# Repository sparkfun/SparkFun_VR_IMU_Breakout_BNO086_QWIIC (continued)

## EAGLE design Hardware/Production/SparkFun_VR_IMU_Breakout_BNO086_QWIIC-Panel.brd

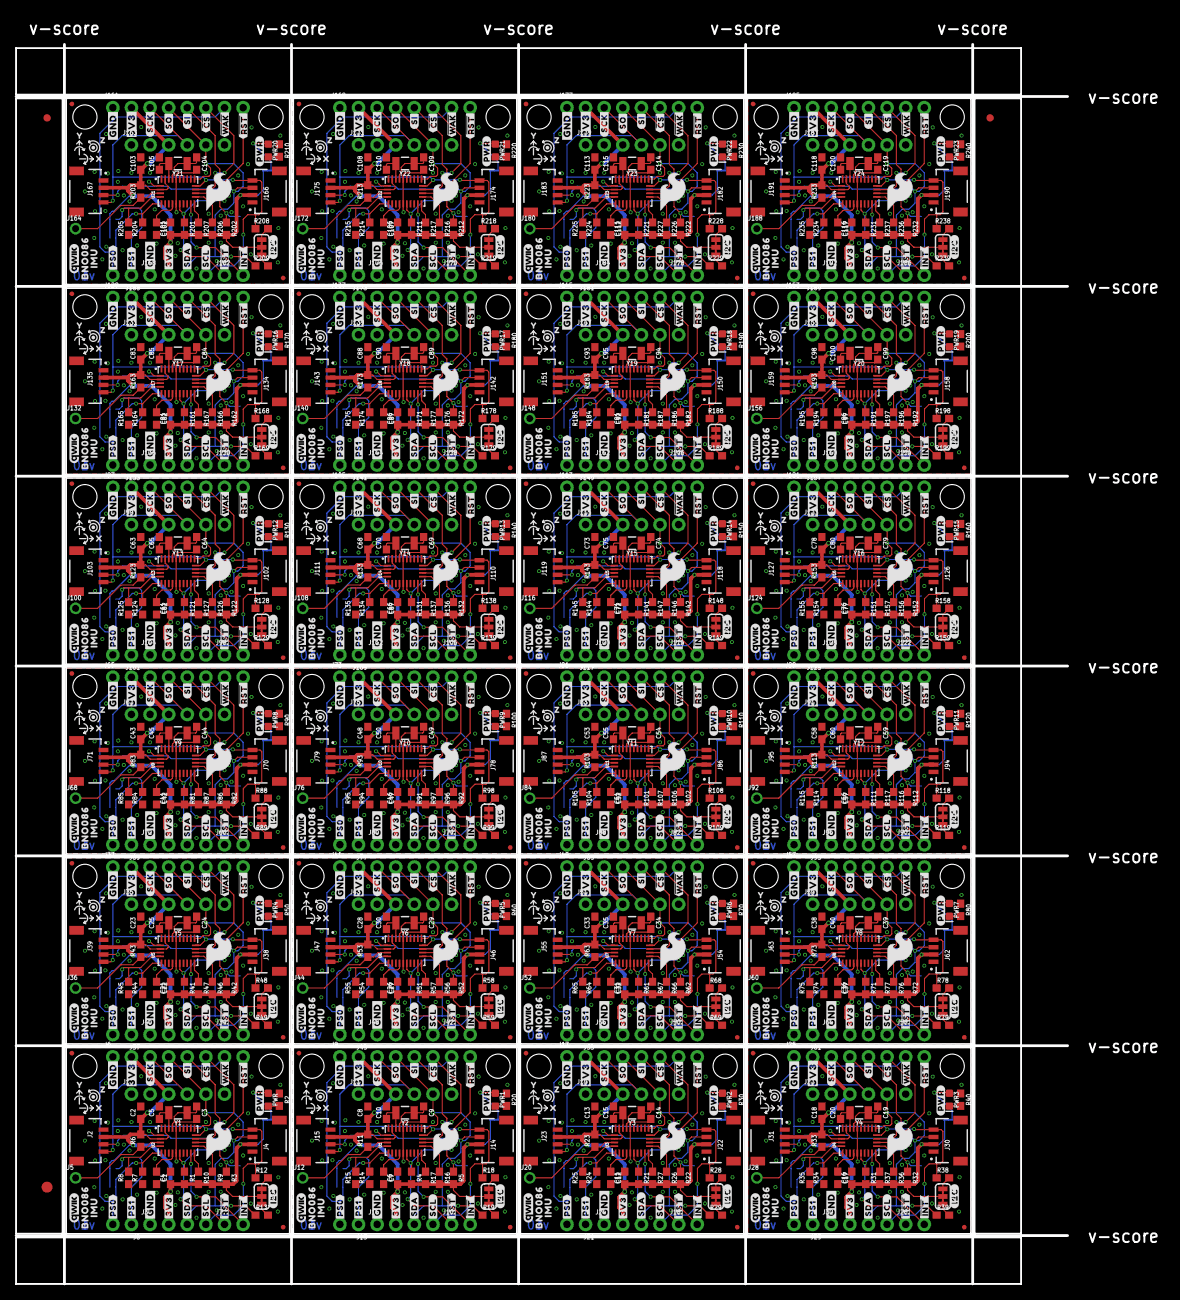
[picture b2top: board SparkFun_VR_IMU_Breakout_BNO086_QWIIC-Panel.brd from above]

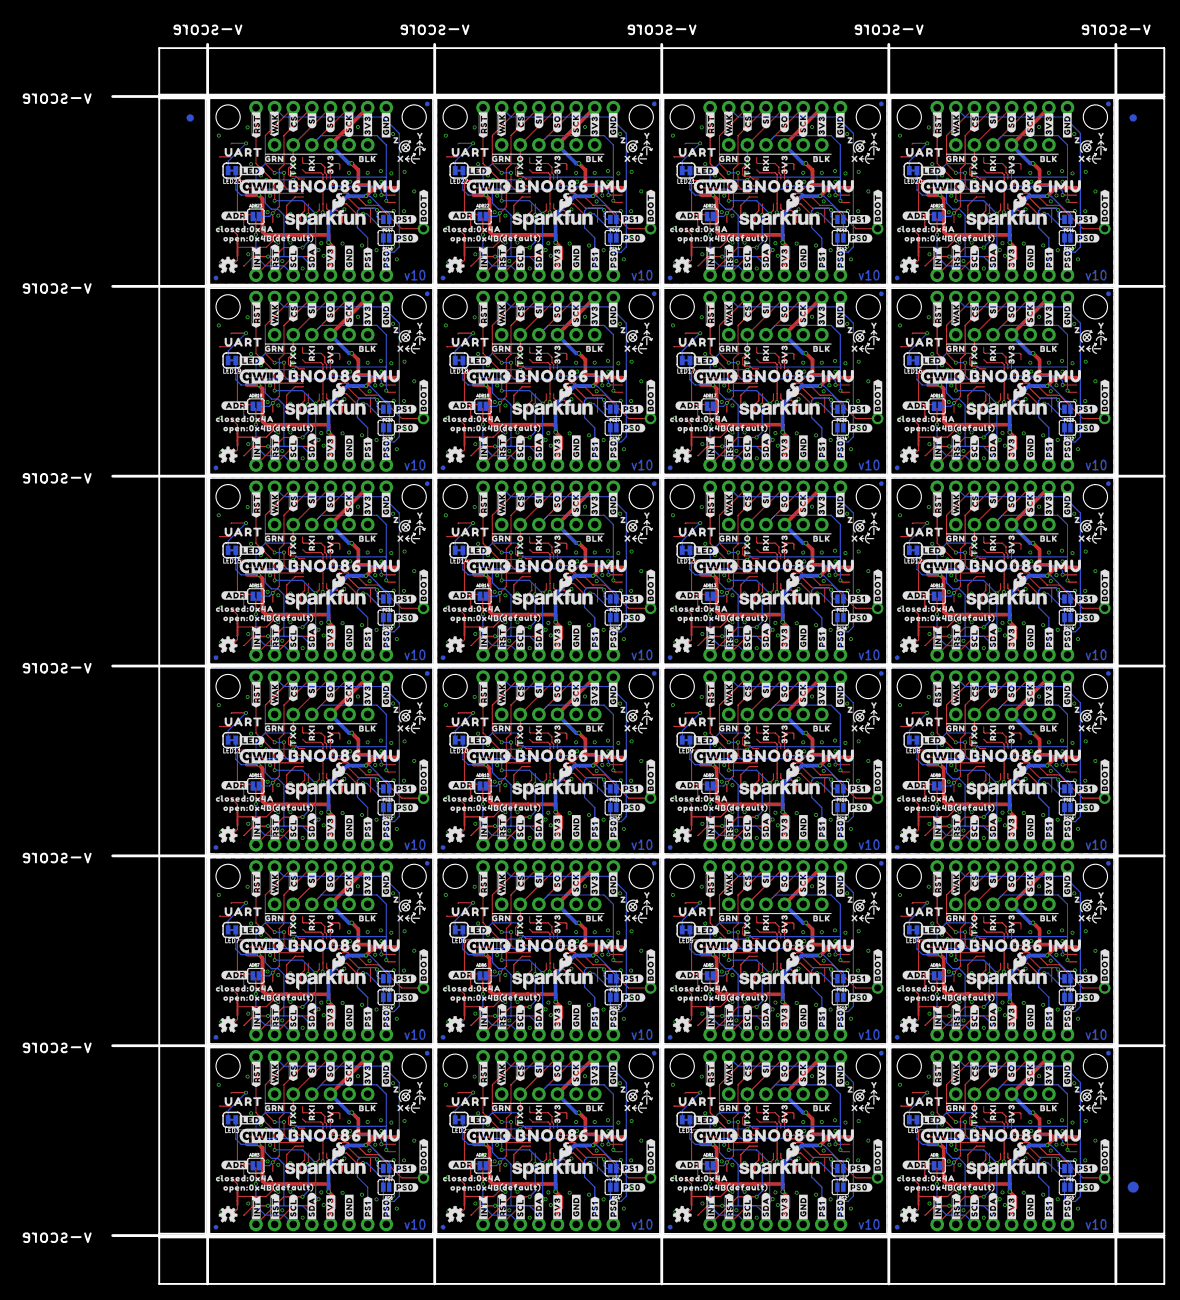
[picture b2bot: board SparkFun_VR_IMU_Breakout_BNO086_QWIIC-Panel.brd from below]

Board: 2 copper layers, 143.5 x 169.2 mm, 2406 parts (1035 on the bottom side), 480 nets.

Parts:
ADR, ADR1, ADR2, ADR3, ADR4, ADR5, ADR6, ADR7, ADR8, ADR9, ADR10, ADR11, ADR12, ADR13, ADR14, ADR15, ADR16, ADR17, ADR18, ADR19, ADR20, ADR21, ADR22, ADR23: SMT-JUMPER_2_NO_SILK
C1, C2, C4, C6, C7, C8, C11, C12, C13, C16, C17, C18, C21, C22, C23, C26, C27, C28, C31, C32, C33, C36, C37, C38, C41, C42, C43, C46, C47, C48, C51, C52, C53, C56, C57, C58, C61, C62, C63, C66, C67, C68, C71, C72, C73, C76, C77, C78, C81, C82, C83, C86, C87, C88, C91, C92, C93, C96, C97, C98, C101, C102, C103, C106, C107, C108, C111, C112, C113, C116, C117, C118: 0.1uF; 0603
C3, C5, C9, C10, C14, C15, C19, C20, C24, C25, C29, C30, C34, C35, C39, C40, C44, C45, C49, C50, C54, C55, C59, C60, C64, C65, C69, C70, C74, C75, C79, C80, C84, C85, C89, C90, C94, C95, C99, C100, C104, C105, C109, C110, C114, C115, C119, C120: 22pF; 0603
E$1, E$2, E$3, E$4: FIDUCIAL-1X2
E$5, E$6: FIDUCIAL-1.5X3
I2C, I2C1, I2C2, I2C3, I2C4, I2C5, I2C6, I2C7, I2C8, I2C9, I2C10, I2C11, I2C12, I2C13, I2C14, I2C15, I2C16, I2C17, I2C18, I2C19, I2C20, I2C21, I2C22, I2C23: SMT-JUMPER_3_2-NC_TRACE_SILK
J1, J11, J19, J27, J35, J43, J51, J59, J67, J75, J83, J91, J99, J107, J115, J123, J131, J139, J147, J155, J163, J171, J179, J187: 1X06_NO_SILK
J2, J4, J14, J15, J22, J23, J30, J31, J38, J39, J46, J47, J54, J55, J62, J63, J70, J71, J78, J79, J86, J87, J94, J95, J102, J103, J110, J111, J118, J119, J126, J127, J134, J135, J142, J143, J150, J151, J158, J159, J166, J167, J174, J175, J182, J183, J190, J191: SMD; JST04_1MM_RA
J3, J16, J24, J32, J40, J48, J56, J64, J72, J80, J88, J96, J104, J112, J120, J128, J136, J144, J152, J160, J168, J176, J184, J192: PTH; 1X04_NO_SILK
J5, J12, J20, J28, J36, J44, J52, J60, J68, J76, J84, J92, J100, J108, J116, J124, J132, J140, J148, J156, J164, J172, J180, J188: 1X01_NO_SILK
J6, J9, J17, J25, J33, J41, J49, J57, J65, J73, J81, J89, J97, J105, J113, J121, J129, J137, J145, J153, J161, J169, J177, J185: SPI; 1X08_NO_SILK
J7, J8, J10, J13, J18, J21, J26, J29, J34, J37, J42, J45, J50, J53, J58, J61, J66, J69, J74, J77, J82, J85, J90, J93, J98, J101, J106, J109, J114, J117, J122, J125, J130, J133, J138, J141, J146, J149, J154, J157, J162, J165, J170, J173, J178, J181, J186, J189: 1X02_NO_SILK
JP1, JP2, JP5, JP6, JP9, JP10, JP11, JP12, JP15, JP16, JP17, JP18, JP21, JP22, JP23, JP24, JP27, JP28, JP29, JP30, JP33, JP34, JP35, JP36, JP39, JP40, JP41, JP42, JP45, JP46, JP47, JP48, JP51, JP52, JP53, JP54, JP57, JP58, JP59, JP60, JP63, JP64, JP65, JP66, JP69, JP70, JP71, JP72, JP75, JP76, JP77, JP78, JP81, JP82, JP83, JP84, JP87, JP88, JP89, JP90, JP93, JP94, JP95, JP96, JP99, JP100, JP101, JP102, JP105, JP106, JP107, JP108, JP111, JP112, JP113, JP114, JP117, JP118, JP119, JP120, JP123, JP124, JP125, JP126, JP129, JP130, JP131, JP132, JP135, JP136, JP137, JP138, JP141, JP142, JP143, JP144: FIDUCIALUFIDUCIAL; FIDUCIAL-MICRO
JP3, JP4, JP7, JP8, JP13, JP14, JP19, JP20, JP25, JP26, JP31, JP32, JP37, JP38, JP43, JP44, JP49, JP50, JP55, JP56, JP61, JP62, JP67, JP68, JP73, JP74, JP79, JP80, JP85, JP86, JP91, JP92, JP97, JP98, JP103, JP104, JP109, JP110, JP115, JP116, JP121, JP122, JP127, JP128, JP133, JP134, JP139, JP140: STAND-OFF
LED, LED1, LED2, LED3, LED4, LED5, LED6, LED7, LED8, LED9, LED10, LED11, LED12, LED13, LED14, LED15, LED16, LED17, LED18, LED19, LED20, LED21, LED22, LED23: SMT-JUMPER_2_NC_TRACE_SILK
LOGO1, LOGO3, LOGO9, LOGO13, LOGO17, LOGO21, LOGO25, LOGO29, LOGO33, LOGO37, LOGO41, LOGO45, LOGO49, LOGO53, LOGO57, LOGO61, LOGO65, LOGO69, LOGO73, LOGO77, LOGO81, LOGO85, LOGO89, LOGO93: OSHW-LOGOMINI; OSHW-LOGO-MINI
LOGO2, LOGO8, LOGO12, LOGO16, LOGO20, LOGO24, LOGO28, LOGO32, LOGO36, LOGO40, LOGO44, LOGO48, LOGO52, LOGO56, LOGO60, LOGO64, LOGO68, LOGO72, LOGO76, LOGO80, LOGO84, LOGO88, LOGO92, LOGO96: REVISION
LOGO4, LOGO6, LOGO10, LOGO14, LOGO18, LOGO22, LOGO26, LOGO30, LOGO34, LOGO38, LOGO42, LOGO46, LOGO50, LOGO54, LOGO58, LOGO62, LOGO66, LOGO70, LOGO74, LOGO78, LOGO82, LOGO86, LOGO90, LOGO94: SFE_LOGO_FLAME.2_INCH; SFE_LOGO_FLAME_.2
LOGO5, LOGO7, LOGO11, LOGO15, LOGO19, LOGO23, LOGO27, LOGO31, LOGO35, LOGO39, LOGO43, LOGO47, LOGO51, LOGO55, LOGO59, LOGO63, LOGO67, LOGO71, LOGO75, LOGO79, LOGO83, LOGO87, LOGO91, LOGO95: SFE_LOGO_NAME_FLAME.1_INCH; SFE_LOGO_NAME_FLAME_.1
PS0, PS1, PS2, PS3, PS4, PS5, PS6, PS7, PS8, PS9, PS10, PS11, PS12, PS13, PS14, PS15, PS16, PS17, PS18, PS19, PS20, PS21, PS22, PS23, PS24, PS25, PS26, PS27, PS28, PS29, PS30, PS31, PS32, PS33, PS34, PS35, PS36, PS37, PS38, PS39, PS40, PS41, PS42, PS43, PS44, PS45, PS46, PS47: SMT-JUMPER_2_NO_SILK
PWR, PWR1, PWR2, PWR3, PWR4, PWR5, PWR6, PWR7, PWR8, PWR9, PWR10, PWR11, PWR12, PWR13, PWR14, PWR15, PWR16, PWR17, PWR18, PWR19, PWR20, PWR21, PWR22, PWR23: RED; LED-0603
R1, R3, R4, R5, R6, R7, R8, R11, R14, R15, R21, R22, R23, R24, R25, R31, R32, R33, R34, R35, R41, R42, R43, R44, R45, R51, R52, R53, R54, R55, R61, R62, R63, R64, R65, R71, R72, R73, R74, R75, R81, R82, R83, R84, R85, R91, R92, R93, R94, R95, R101, R102, R103, R104, R105, R111, R112, R113, R114, R115, R121, R122, R123, R124, R125, R131, R132, R133, R134, R135, R141, R142, R143, R144, R145, R151, R152, R153, R154, R155, R161, R162, R163, R164, R165, R171, R172, R173, R174, R175, R181, R182, R183, R184, R185, R191, R192, R193, R194, R195, R201, R202, R203, R204, R205, R211, R212, R213, R214, R215, R221, R222, R223, R224, R225, R231, R232, R233, R234, R235: 10k; 0603
R2, R9, R10, R16, R17, R20, R26, R27, R30, R36, R37, R40, R46, R47, R50, R56, R57, R60, R66, R67, R70, R76, R77, R80, R86, R87, R90, R96, R97, R100, R106, R107, R110, R116, R117, R120, R126, R127, R130, R136, R137, R140, R146, R147, R150, R156, R157, R160, R166, R167, R170, R176, R177, R180, R186, R187, R190, R196, R197, R200, R206, R207, R210, R216, R217, R220, R226, R227, R230, R236, R237, R240: 4.7k; 0603
R12, R13, R18, R19, R28, R29, R38, R39, R48, R49, R58, R59, R68, R69, R78, R79, R88, R89, R98, R99, R108, R109, R118, R119, R128, R129, R138, R139, R148, R149, R158, R159, R168, R169, R178, R179, R188, R189, R198, R199, R208, R209, R218, R219, R228, R229, R238, R239: 2.2k; 0603
U1, U2, U3, U4, U5, U6, U7, U8, U9, U10, U11, U12, U13, U14, U15, U16, U17, U18, U19, U20, U21, U22, U23, U24: BNO086; LGA-28
U$1, U$71, U$130, U$189, U$248, U$307, U$366, U$425, U$484, U$543, U$602, U$661, U$720, U$779, U$838, U$897, U$956, U$1015, U$1074, U$1133, U$1192, U$1251, U$1310, U$1369: #I2C#874
U$2, U$98, U$157, U$216, U$275, U$334, U$393, U$452, U$511, U$570, U$629, U$688, U$747, U$806, U$865, U$924, U$983, U$1042, U$1101, U$1160, U$1219, U$1278, U$1337, U$1396: BLK889
U$3, U$25, U$80, U$85, U$139, U$144, U$198, U$203, U$257, U$262, U$316, U$321, U$375, U$380, U$434, U$439, U$493, U$498, U$552, U$557, U$611, U$616, U$670, U$675, U$729, U$734, U$788, U$793, U$847, U$852, U$906, U$911, U$965, U$970, U$1024, U$1029, U$1083, U$1088, U$1142, U$1147, U$1201, U$1206, U$1260, U$1265, U$1319, U$1324, U$1378, U$1383: X878
U$4, U$113, U$172, U$231, U$290, U$349, U$408, U$467, U$526, U$585, U$644, U$703, U$762, U$821, U$880, U$939, U$998, U$1057, U$1116, U$1175, U$1234, U$1293, U$1352, U$1411: ##INT##6
U$5, U$112, U$171, U$230, U$289, U$348, U$407, U$466, U$525, U$584, U$643, U$702, U$761, U$820, U$879, U$938, U$997, U$1056, U$1115, U$1174, U$1233, U$1292, U$1351, U$1410: ##RST##5
U$6, U$10, U$81, U$83, U$140, U$142, U$199, U$201, U$258, U$260, U$317, U$319, U$376, U$378, U$435, U$437, U$494, U$496, U$553, U$555, U$612, U$614, U$671, U$673, U$730, U$732, U$789, U$791, U$848, U$850, U$907, U$909, U$966, U$968, U$1025, U$1027, U$1084, U$1086, U$1143, U$1145, U$1202, U$1204, U$1261, U$1263, U$1320, U$1322, U$1379, U$1381: Y879
U$7, U$15, U$82, U$84, U$141, U$143, U$200, U$202, U$259, U$261, U$318, U$320, U$377, U$379, U$436, U$438, U$495, U$497, U$554, U$556, U$613, U$615, U$672, U$674, U$731, U$733, U$790, U$792, U$849, U$851, U$908, U$910, U$967, U$969, U$1026, U$1028, U$1085, U$1087, U$1144, U$1146, U$1203, U$1205, U$1262, U$1264, U$1321, U$1323, U$1380, U$1382: Z880
U$8, U$111, U$170, U$229, U$288, U$347, U$406, U$465, U$524, U$583, U$642, U$701, U$760, U$819, U$878, U$937, U$996, U$1055, U$1114, U$1173, U$1232, U$1291, U$1350, U$1409: #SCL#4
U$9, U$16, U$109, U$114, U$168, U$173, U$227, U$232, U$286, U$291, U$345, U$350, U$404, U$409, U$463, U$468, U$522, U$527, U$581, U$586, U$640, U$645, U$699, U$704, U$758, U$763, U$817, U$822, U$876, U$881, U$935, U$940, U$994, U$999, U$1053, U$1058, U$1112, U$1117, U$1171, U$1176, U$1230, U$1235, U$1289, U$1294, U$1348, U$1353, U$1407, U$1412: #GND#2
U$11, U$91, U$150, U$209, U$268, U$327, U$386, U$445, U$504, U$563, U$622, U$681, U$740, U$799, U$858, U$917, U$976, U$1035, U$1094, U$1153, U$1212, U$1271, U$1330, U$1389: #SCK#882
U$12, U$65, U$124, U$183, U$242, U$301, U$360, U$419, U$478, U$537, U$596, U$655, U$714, U$773, U$832, U$891, U$950, U$1009, U$1068, U$1127, U$1186, U$1245, U$1304, U$1363: #SO#867
U$13, U$66, U$125, U$184, U$243, U$302, U$361, U$420, U$479, U$538, U$597, U$656, U$715, U$774, U$833, U$892, U$951, U$1010, U$1069, U$1128, U$1187, U$1246, U$1305, U$1364: #SI#868
U$14, U$110, U$169, U$228, U$287, U$346, U$405, U$464, U$523, U$582, U$641, U$700, U$759, U$818, U$877, U$936, U$995, U$1054, U$1113, U$1172, U$1231, U$1290, U$1349, U$1408: #SDA#3
U$17, U$67, U$126, U$185, U$244, U$303, U$362, U$421, U$480, U$539, U$598, U$657, U$716, U$775, U$834, U$893, U$952, U$1011, U$1070, U$1129, U$1188, U$1247, U$1306, U$1365: ##CS##870
U$18, U$94, U$153, U$212, U$271, U$330, U$389, U$448, U$507, U$566, U$625, U$684, U$743, U$802, U$861, U$920, U$979, U$1038, U$1097, U$1156, U$1215, U$1274, U$1333, U$1392: ##CS##885
U$19, U$69, U$128, U$187, U$246, U$305, U$364, U$423, U$482, U$541, U$600, U$659, U$718, U$777, U$836, U$895, U$954, U$1013, U$1072, U$1131, U$1190, U$1249, U$1308, U$1367: ##RST##872
U$20, U$96, U$155, U$214, U$273, U$332, U$391, U$450, U$509, U$568, U$627, U$686, U$745, U$804, U$863, U$922, U$981, U$1040, U$1099, U$1158, U$1217, U$1276, U$1335, U$1394: ##RST##887
U$21, U$101, U$160, U$219, U$278, U$337, U$396, U$455, U$514, U$573, U$632, U$691, U$750, U$809, U$868, U$927, U$986, U$1045, U$1104, U$1163, U$1222, U$1281, U$1340, U$1399: RXI891
U$22, U$102, U$161, U$220, U$279, U$338, U$397, U$456, U$515, U$574, U$633, U$692, U$751, U$810, U$869, U$928, U$987, U$1046, U$1105, U$1164, U$1223, U$1282, U$1341, U$1400: TXO892
U$23, U$72, U$131, U$190, U$249, U$308, U$367, U$426, U$485, U$544, U$603, U$662, U$721, U$780, U$839, U$898, U$957, U$1016, U$1075, U$1134, U$1193, U$1252, U$1311, U$1370: #PS0#874
U$24, U$59, U$119, U$178, U$237, U$296, U$355, U$414, U$473, U$532, U$591, U$650, U$709, U$768, U$827, U$886, U$945, U$1004, U$1063, U$1122, U$1181, U$1240, U$1299, U$1358: BNO0861
U$26, U$115, U$174, U$233, U$292, U$351, U$410, U$469, U$528, U$587, U$646, U$705, U$764, U$823, U$882, U$941, U$1000, U$1059, U$1118, U$1177, U$1236, U$1295, U$1354, U$1413: #LED#0
U$27, U$46, U$75, U$108, U$134, U$167, U$193, U$226, U$252, U$285, U$311, U$344, U$370, U$403, U$429, U$462, U$488, U$521, U$547, U$580, U$606, U$639, U$665, U$698, U$724, U$757, U$783, U$816, U$842, U$875, U$901, U$934, U$960, U$993, U$1019, U$1052, U$1078, U$1111, U$1137, U$1170, U$1196, U$1229, U$1255, U$1288, U$1314, U$1347, U$1373, U$1406: #3V3#874
U$28, U$116, U$175, U$234, U$293, U$352, U$411, U$470, U$529, U$588, U$647, U$706, U$765, U$824, U$883, U$942, U$1001, U$1060, U$1119, U$1178, U$1237, U$1296, U$1355, U$1414: OPEN#0X4B0
U$29, U$86, U$145, U$204, U$263, U$322, U$381, U$440, U$499, U$558, U$617, U$676, U$735, U$794, U$853, U$912, U$971, U$1030, U$1089, U$1148, U$1207, U$1266, U$1325, U$1384: QWIIC_4MM
U$30, U$103, U$162, U$221, U$280, U$339, U$398, U$457, U$516, U$575, U$634, U$693, U$752, U$811, U$870, U$929, U$988, U$1047, U$1106, U$1165, U$1224, U$1283, U$1342, U$1401: #ADR#894
U$31, U$60, U$120, U$179, U$238, U$297, U$356, U$415, U$474, U$533, U$592, U$651, U$710, U$769, U$828, U$887, U$946, U$1005, U$1064, U$1123, U$1182, U$1241, U$1300, U$1359: IMU862
U$32, U$45, U$62, U$74, U$121, U$133, U$180, U$192, U$239, U$251, U$298, U$310, U$357, U$369, U$416, U$428, U$475, U$487, U$534, U$546, U$593, U$605, U$652, U$664, U$711, U$723, U$770, U$782, U$829, U$841, U$888, U$900, U$947, U$959, U$1006, U$1018, U$1065, U$1077, U$1124, U$1136, U$1183, U$1195, U$1242, U$1254, U$1301, U$1313, U$1360, U$1372: #GND#864
U$33, U$106, U$165, U$224, U$283, U$342, U$401, U$460, U$519, U$578, U$637, U$696, U$755, U$814, U$873, U$932, U$991, U$1050, U$1109, U$1168, U$1227, U$1286, U$1345, U$1404: #PS1#1
U$34, U$107, U$166, U$225, U$284, U$343, U$402, U$461, U$520, U$579, U$638, U$697, U$756, U$815, U$874, U$933, U$992, U$1051, U$1110, U$1169, U$1228, U$1287, U$1346, U$1405: #PS0#2
U$35, U$104, U$163, U$222, U$281, U$340, U$399, U$458, U$517, U$576, U$635, U$694, U$753, U$812, U$871, U$930, U$989, U$1048, U$1107, U$1166, U$1225, U$1284, U$1343, U$1402: #PS1#895
U$36, U$63, U$122, U$181, U$240, U$299, U$358, U$417, U$476, U$535, U$594, U$653, U$712, U$771, U$830, U$889, U$948, U$1007, U$1066, U$1125, U$1184, U$1243, U$1302, U$1361: #3V3#865
U$37, U$64, U$123, U$182, U$241, U$300, U$359, U$418, U$477, U$536, U$595, U$654, U$713, U$772, U$831, U$890, U$949, U$1008, U$1067, U$1126, U$1185, U$1244, U$1303, U$1362: #SCK#866
U$38, U$68, U$127, U$186, U$245, U$304, U$363, U$422, U$481, U$540, U$599, U$658, U$717, U$776, U$835, U$894, U$953, U$1012, U$1071, U$1130, U$1189, U$1248, U$1307, U$1366: ##WAK##871
U$39, U$90, U$149, U$208, U$267, U$326, U$385, U$444, U$503, U$562, U$621, U$680, U$739, U$798, U$857, U$916, U$975, U$1034, U$1093, U$1152, U$1211, U$1270, U$1329, U$1388: #3V3#882
U$40, U$100, U$159, U$218, U$277, U$336, U$395, U$454, U$513, U$572, U$631, U$690, U$749, U$808, U$867, U$926, U$985, U$1044, U$1103, U$1162, U$1221, U$1280, U$1339, U$1398: 3V3891
U$41, U$99, U$158, U$217, U$276, U$335, U$394, U$453, U$512, U$571, U$630, U$689, U$748, U$807, U$866, U$925, U$984, U$1043, U$1102, U$1161, U$1220, U$1279, U$1338, U$1397: GRN890
U$42, U$70, U$129, U$188, U$247, U$306, U$365, U$424, U$483, U$542, U$601, U$660, U$719, U$778, U$837, U$896, U$955, U$1014, U$1073, U$1132, U$1191, U$1250, U$1309, U$1368: #PWR#873
U$43, U$73, U$132, U$191, U$250, U$309, U$368, U$427, U$486, U$545, U$604, U$663, U$722, U$781, U$840, U$899, U$958, U$1017, U$1076, U$1135, U$1194, U$1253, U$1312, U$1371: #PS1#874
U$44, U$89, U$148, U$207, U$266, U$325, U$384, U$443, U$502, U$561, U$620, U$679, U$738, U$797, U$856, U$915, U$974, U$1033, U$1092, U$1151, U$1210, U$1269, U$1328, U$1387: UART881
U$47, U$76, U$135, U$194, U$253, U$312, U$371, U$430, U$489, U$548, U$607, U$666, U$725, U$784, U$843, U$902, U$961, U$1020, U$1079, U$1138, U$1197, U$1256, U$1315, U$1374: #SDA#874
U$48, U$77, U$136, U$195, U$254, U$313, U$372, U$431, U$490, U$549, U$608, U$667, U$726, U$785, U$844, U$903, U$962, U$1021, U$1080, U$1139, U$1198, U$1257, U$1316, U$1375: #SCL#875
U$49, U$97, U$156, U$215, U$274, U$333, U$392, U$451, U$510, U$569, U$628, U$687, U$746, U$805, U$864, U$923, U$982, U$1041, U$1100, U$1159, U$1218, U$1277, U$1336, U$1395: #BOOT#888
U$50, U$78, U$137, U$196, U$255, U$314, U$373, U$432, U$491, U$550, U$609, U$668, U$727, U$786, U$845, U$904, U$963, U$1022, U$1081, U$1140, U$1199, U$1258, U$1317, U$1376: ##RST##876
U$51, U$79, U$138, U$197, U$256, U$315, U$374, U$433, U$492, U$551, U$610, U$669, U$728, U$787, U$846, U$905, U$964, U$1023, U$1082, U$1141, U$1200, U$1259, U$1318, U$1377: ##INT##877
U$52, U$87, U$146, U$205, U$264, U$323, U$382, U$441, U$500, U$559, U$618, U$677, U$736, U$795, U$854, U$913, U$972, U$1031, U$1090, U$1149, U$1208, U$1267, U$1326, U$1385: QWIIC_6MM
U$53, U$95, U$154, U$213, U$272, U$331, U$390, U$449, U$508, U$567, U$626, U$685, U$744, U$803, U$862, U$921, U$980, U$1039, U$1098, U$1157, U$1216, U$1275, U$1334, U$1393: ##WAK##886
U$54, U$88, U$147, U$206, U$265, U$324, U$383, U$442, U$501, U$560, U$619, U$678, U$737, U$796, U$855, U$914, U$973, U$1032, U$1091, U$1150, U$1209, U$1268, U$1327, U$1386: BNO086_IMU881
U$55, U$92, U$151, U$210, U$269, U$328, U$387, U$446, U$505, U$564, U$623, U$682, U$741, U$800, U$859, U$918, U$977, U$1036, U$1095, U$1154, U$1213, U$1272, U$1331, U$1390: #SO#883
U$56, U$93, U$152, U$211, U$270, U$329, U$388, U$447, U$506, U$565, U$624, U$683, U$742, U$801, U$860, U$919, U$978, U$1037, U$1096, U$1155, U$1214, U$1273, U$1332, U$1391: #SI#884
U$57, U$105, U$164, U$223, U$282, U$341, U$400, U$459, U$518, U$577, U$636, U$695, U$754, U$813, U$872, U$931, U$990, U$1049, U$1108, U$1167, U$1226, U$1285, U$1344, U$1403: #PS0#895
U$58, U$117, U$176, U$235, U$294, U$353, U$412, U$471, U$530, U$589, U$648, U$707, U$766, U$825, U$884, U$943, U$1002, U$1061, U$1120, U$1179, U$1238, U$1297, U$1356, U$1415: CLOSED#0X4A0
U$61, U$118, U$177, U$236, U$295, U$354, U$413, U$472, U$531, U$590, U$649, U$708, U$767, U$826, U$885, U$944, U$1003, U$1062, U$1121, U$1180, U$1239, U$1298, U$1357, U$1416: DEFAULT0
Y1, Y2, Y3, Y4, Y5, Y6, Y7, Y8, Y9, Y10, Y11, Y12, Y13, Y14, Y15, Y16, Y17, Y18, Y19, Y20, Y21, Y22, Y23, Y24: 32.768kHz; CRYSTAL-SMD-3.2X1.5MM

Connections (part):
3.3V: C2.1, C4.1, I2C.2, J1.3, J2.2, J3.2, J4.2, J6.2, LED.1, PS0.1, PS1.1, R1.2, R3.2, R6.2, R9.2, R10.2, U2.3, U2.28
3.3V1: C6.1, C8.1, I2C1.2, J9.2, J11.3, J14.2, J15.2, J16.2, LED1.1, PS2.1, PS3.1, R4.2, R5.2, R11.2, R16.2, R17.2, U1.3, U1.28
3.3V2: C11.1, C13.1, I2C2.2, J17.2, J19.3, J22.2, J23.2, J24.2, LED2.1, PS4.1, PS5.1, R21.2, R22.2, R23.2, R26.2, R27.2, U3.3, U3.28
3.3V3: C16.1, C18.1, I2C3.2, J25.2, J27.3, J30.2, J31.2, J32.2, LED3.1, PS6.1, PS7.1, R31.2, R32.2, R33.2, R36.2, R37.2, U4.3, U4.28
3.3V4: C21.1, C23.1, I2C4.2, J33.2, J35.3, J38.2, J39.2, J40.2, LED4.1, PS8.1, PS9.1, R41.2, R42.2, R43.2, R46.2, R47.2, U5.3, U5.28
3.3V5: C26.1, C28.1, I2C5.2, J41.2, J43.3, J46.2, J47.2, J48.2, LED5.1, PS10.1, PS11.1, R51.2, R52.2, R53.2, R56.2, R57.2, U6.3, U6.28
3.3V6: C31.1, C33.1, I2C6.2, J49.2, J51.3, J54.2, J55.2, J56.2, LED6.1, PS12.1, PS13.1, R61.2, R62.2, R63.2, R66.2, R67.2, U7.3, U7.28
3.3V7: C36.1, C38.1, I2C7.2, J57.2, J59.3, J62.2, J63.2, J64.2, LED7.1, PS14.1, PS15.1, R71.2, R72.2, R73.2, R76.2, R77.2, U8.3, U8.28
3.3V8: C41.1, C43.1, I2C8.2, J65.2, J67.3, J70.2, J71.2, J72.2, LED8.1, PS16.1, PS17.1, R81.2, R82.2, R83.2, R86.2, R87.2, U9.3, U9.28
3.3V9: C46.1, C48.1, I2C9.2, J73.2, J75.3, J78.2, J79.2, J80.2, LED9.1, PS18.1, PS19.1, R91.2, R92.2, R93.2, R96.2, R97.2, U10.3, U10.28
3.3V10: C51.1, C53.1, I2C10.2, J81.2, J83.3, J86.2, J87.2, J88.2, LED10.1, PS20.1, PS21.1, R101.2, R102.2, R103.2, R106.2, R107.2, U11.3, U11.28
3.3V11: C56.1, C58.1, I2C11.2, J89.2, J91.3, J94.2, J95.2, J96.2, LED11.1, PS22.1, PS23.1, R111.2, R112.2, R113.2, R116.2, R117.2, U12.3, U12.28
3.3V12: C61.1, C63.1, I2C12.2, J97.2, J99.3, J102.2, J103.2, J104.2, LED12.1, PS24.1, PS25.1, R121.2, R122.2, R123.2, R126.2, R127.2, U13.3, U13.28
3.3V13: C66.1, C68.1, I2C13.2, J105.2, J107.3, J110.2, J111.2, J112.2, LED13.1, PS26.1, PS27.1, R131.2, R132.2, R133.2, R136.2, R137.2, U14.3, U14.28
3.3V14: C71.1, C73.1, I2C14.2, J113.2, J115.3, J118.2, J119.2, J120.2, LED14.1, PS28.1, PS29.1, R141.2, R142.2, R143.2, R146.2, R147.2, U15.3, U15.28
3.3V15: C76.1, C78.1, I2C15.2, J121.2, J123.3, J126.2, J127.2, J128.2, LED15.1, PS30.1, PS31.1, R151.2, R152.2, R153.2, R156.2, R157.2, U16.3, U16.28
3.3V16: C81.1, C83.1, I2C16.2, J129.2, J131.3, J134.2, J135.2, J136.2, LED16.1, PS32.1, PS33.1, R161.2, R162.2, R163.2, R166.2, R167.2, U17.3, U17.28
3.3V17: C86.1, C88.1, I2C17.2, J137.2, J139.3, J142.2, J143.2, J144.2, LED17.1, PS34.1, PS35.1, R171.2, R172.2, R173.2, R176.2, R177.2, U18.3, U18.28
3.3V18: C91.1, C93.1, I2C18.2, J145.2, J147.3, J150.2, J151.2, J152.2, LED18.1, PS36.1, PS37.1, R181.2, R182.2, R183.2, R186.2, R187.2, U19.3, U19.28
3.3V19: C96.1, C98.1, I2C19.2, J153.2, J155.3, J158.2, J159.2, J160.2, LED19.1, PS38.1, PS39.1, R191.2, R192.2, R193.2, R196.2, R197.2, U20.3, U20.28
3.3V20: C101.1, C103.1, I2C20.2, J161.2, J163.3, J166.2, J167.2, J168.2, LED20.1, PS40.1, PS41.1, R201.2, R202.2, R203.2, R206.2, R207.2, U21.3, U21.28
3.3V21: C106.1, C108.1, I2C21.2, J169.2, J171.3, J174.2, J175.2, J176.2, LED21.1, PS42.1, PS43.1, R211.2, R212.2, R213.2, R216.2, R217.2, U22.3, U22.28
3.3V22: C111.1, C113.1, I2C22.2, J177.2, J179.3, J182.2, J183.2, J184.2, LED22.1, PS44.1, PS45.1, R221.2, R222.2, R223.2, R226.2, R227.2, U23.3, U23.28
3.3V23: C116.1, C118.1, I2C23.2, J185.2, J187.3, J190.2, J191.2, J192.2, LED23.1, PS46.1, PS47.1, R231.2, R232.2, R233.2, R236.2, R237.2, U24.3, U24.28
!BOOT: J5.1, R6.1, U2.4
!BOOT1: J12.1, R11.1, U1.4
!BOOT2: J20.1, R23.1, U3.4
!BOOT3: J28.1, R33.1, U4.4
!BOOT4: J36.1, R43.1, U5.4
!BOOT5: J44.1, R53.1, U6.4
!BOOT6: J52.1, R63.1, U7.4
!BOOT7: J60.1, R73.1, U8.4
!BOOT8: J68.1, R83.1, U9.4
!BOOT9: J76.1, R93.1, U10.4
!BOOT10: J84.1, R103.1, U11.4
!BOOT11: J92.1, R113.1, U12.4
!BOOT12: J100.1, R123.1, U13.4
!BOOT13: J108.1, R133.1, U14.4
!BOOT14: J116.1, R143.1, U15.4
!BOOT15: J124.1, R153.1, U16.4
!BOOT16: J132.1, R163.1, U17.4
!BOOT17: J140.1, R173.1, U18.4
!BOOT18: J148.1, R183.1, U19.4
!BOOT19: J156.1, R193.1, U20.4
!BOOT20: J164.1, R203.1, U21.4
!BOOT21: J172.1, R213.1, U22.4
!BOOT22: J180.1, R223.1, U23.4
!BOOT23: J188.1, R233.1, U24.4
!CS: J6.6, U2.18
!CS1: J9.6, U1.18
!CS2: J17.6, U3.18
!CS3: J25.6, U4.18
!CS4: J33.6, U5.18
!CS5: J41.6, U6.18
!CS6: J49.6, U7.18
!CS7: J57.6, U8.18
!CS8: J65.6, U9.18
!CS9: J73.6, U10.18
!CS10: J81.6, U11.18
!CS11: J89.6, U12.18
!CS12: J97.6, U13.18
!CS13: J105.6, U14.18
!CS14: J113.6, U15.18
!CS15: J121.6, U16.18
!CS16: J129.6, U17.18
!CS17: J137.6, U18.18
!CS18: J145.6, U19.18
!CS19: J153.6, U20.18
!CS20: J161.6, U21.18
!CS21: J169.6, U22.18
!CS22: J177.6, U23.18
!CS23: J185.6, U24.18
!INT: J7.2, U2.14
!INT1: J10.2, U1.14
!INT2: J18.2, U3.14
!INT3: J26.2, U4.14
!INT4: J34.2, U5.14
!INT5: J42.2, U6.14
!INT6: J50.2, U7.14
!INT7: J58.2, U8.14
!INT8: J66.2, U9.14
!INT9: J74.2, U10.14
!INT10: J82.2, U11.14
!INT11: J90.2, U12.14
!INT12: J98.2, U13.14
!INT13: J106.2, U14.14
!INT14: J114.2, U15.14
!INT15: J122.2, U16.14
!INT16: J130.2, U17.14
!INT17: J138.2, U18.14
!INT18: J146.2, U19.14
!INT19: J154.2, U20.14
!INT20: J162.2, U21.14
!INT21: J170.2, U22.14
!INT22: J178.2, U23.14
!INT23: J186.2, U24.14
!RST: J6.8, J7.1, R1.1, U2.11
!RST1: J9.8, J10.1, R4.1, U1.11
!RST2: J17.8, J18.1, R21.1, U3.11
!RST3: J25.8, J26.1, R31.1, U4.11
!RST4: J33.8, J34.1, R41.1, U5.11
!RST5: J41.8, J42.1, R51.1, U6.11
!RST6: J49.8, J50.1, R61.1, U7.11
!RST7: J57.8, J58.1, R71.1, U8.11
!RST8: J65.8, J66.1, R81.1, U9.11
!RST9: J73.8, J74.1, R91.1, U10.11
!RST10: J81.8, J82.1, R101.1, U11.11
!RST11: J89.8, J90.1, R111.1, U12.11
!RST12: J97.8, J98.1, R121.1, U13.11
!RST13: J105.8, J106.1, R131.1, U14.11
!RST14: J113.8, J114.1, R141.1, U15.11
!RST15: J121.8, J122.1, R151.1, U16.11
!RST16: J129.8, J130.1, R161.1, U17.11
!RST17: J137.8, J138.1, R171.1, U18.11
!RST18: J145.8, J146.1, R181.1, U19.11
!RST19: J153.8, J154.1, R191.1, U20.11
!RST20: J161.8, J162.1, R201.1, U21.11
!RST21: J169.8, J170.1, R211.1, U22.11
!RST22: J177.8, J178.1, R221.1, U23.11
!RST23: J185.8, J186.1, R231.1, U24.11
ADDR/MOSI: ADR.2, J6.5, R3.1, U2.17
ADDR/MOSI1: ADR1.2, J9.5, R5.1, U1.17
ADDR/MOSI2: ADR2.2, J17.5, R22.1, U3.17
ADDR/MOSI3: ADR3.2, J25.5, R32.1, U4.17
ADDR/MOSI4: ADR4.2, J33.5, R42.1, U5.17
ADDR/MOSI5: ADR5.2, J41.5, R52.1, U6.17
ADDR/MOSI6: ADR6.2, J49.5, R62.1, U7.17
ADDR/MOSI7: ADR7.2, J57.5, R72.1, U8.17
ADDR/MOSI8: ADR8.2, J65.5, R82.1, U9.17
ADDR/MOSI9: ADR9.2, J73.5, R92.1, U10.17
ADDR/MOSI10: ADR10.2, J81.5, R102.1, U11.17
ADDR/MOSI11: ADR11.2, J89.5, R112.1, U12.17
ADDR/MOSI12: ADR12.2, J97.5, R122.1, U13.17
ADDR/MOSI13: ADR13.2, J105.5, R132.1, U14.17
ADDR/MOSI14: ADR14.2, J113.5, R142.1, U15.17
ADDR/MOSI15: ADR15.2, J121.5, R152.1, U16.17
ADDR/MOSI16: ADR16.2, J129.5, R162.1, U17.17
ADDR/MOSI17: ADR17.2, J137.5, R172.1, U18.17
ADDR/MOSI18: ADR18.2, J145.5, R182.1, U19.17
ADDR/MOSI19: ADR19.2, J153.5, R192.1, U20.17
ADDR/MOSI20: ADR20.2, J161.5, R202.1, U21.17
ADDR/MOSI21: ADR21.2, J169.5, R212.1, U22.17
ADDR/MOSI22: ADR22.2, J177.5, R222.1, U23.17
ADDR/MOSI23: ADR23.2, J185.5, R232.1, U24.17
CAP: C1.1, U2.9
CAP1: C7.1, U1.9
CAP2: C12.1, U3.9
CAP3: C17.1, U4.9
CAP4: C22.1, U5.9
CAP5: C27.1, U6.9
CAP6: C32.1, U7.9
CAP7: C37.1, U8.9
CAP8: C42.1, U9.9
CAP9: C47.1, U10.9
CAP10: C52.1, U11.9
CAP11: C57.1, U12.9
CAP12: C62.1, U13.9
CAP13: C67.1, U14.9
CAP14: C72.1, U15.9
CAP15: C77.1, U16.9
CAP16: C82.1, U17.9
CAP17: C87.1, U18.9
CAP18: C92.1, U19.9
CAP19: C97.1, U20.9
CAP20: C102.1, U21.9
CAP21: C107.1, U22.9
CAP22: C112.1, U23.9
CAP23: C117.1, U24.9
GND: ADR.1, C1.2, C2.2, C3.2, C4.2, C5.2, J1.1, J2.1, J3.1, J4.1, J6.1, R2.1, R7.1, R8.1, U2.2, U2.10, U2.25
GND1: ADR1.1, C6.2, C7.2, C8.2, C9.2, C10.2, J9.1, J11.1, J14.1, J15.1, J16.1, R14.1, R15.1, R20.1, U1.2, U1.10, U1.25
GND2: ADR2.1, C11.2, C12.2, C13.2, C14.2, C15.2, J17.1, J19.1, J22.1, J23.1, J24.1, R24.1, R25.1, R30.1, U3.2, U3.10, U3.25
GND3: ADR3.1, C16.2, C17.2, C18.2, C19.2, C20.2, J25.1, J27.1, J30.1, J31.1, J32.1, R34.1, R35.1, R40.1, U4.2, U4.10, U4.25
GND4: ADR4.1, C21.2, C22.2, C23.2, C24.2, C25.2, J33.1, J35.1, J38.1, J39.1, J40.1, R44.1, R45.1, R50.1, U5.2, U5.10, U5.25
GND5: ADR5.1, C26.2, C27.2, C28.2, C29.2, C30.2, J41.1, J43.1, J46.1, J47.1, J48.1, R54.1, R55.1, R60.1, U6.2, U6.10, U6.25
GND6: ADR6.1, C31.2, C32.2, C33.2, C34.2, C35.2, J49.1, J51.1, J54.1, J55.1, J56.1, R64.1, R65.1, R70.1, U7.2, U7.10, U7.25
GND7: ADR7.1, C36.2, C37.2, C38.2, C39.2, C40.2, J57.1, J59.1, J62.1, J63.1, J64.1, R74.1, R75.1, R80.1, U8.2, U8.10, U8.25
GND8: ADR8.1, C41.2, C42.2, C43.2, C44.2, C45.2, J65.1, J67.1, J70.1, J71.1, J72.1, R84.1, R85.1, R90.1, U9.2, U9.10, U9.25
GND9: ADR9.1, C46.2, C47.2, C48.2, C49.2, C50.2, J73.1, J75.1, J78.1, J79.1, J80.1, R94.1, R95.1, R100.1, U10.2, U10.10, U10.25
GND10: ADR10.1, C51.2, C52.2, C53.2, C54.2, C55.2, J81.1, J83.1, J86.1, J87.1, J88.1, R104.1, R105.1, R110.1, U11.2, U11.10, U11.25
GND11: ADR11.1, C56.2, C57.2, C58.2, C59.2, C60.2, J89.1, J91.1, J94.1, J95.1, J96.1, R114.1, R115.1, R120.1, U12.2, U12.10, U12.25
GND12: ADR12.1, C61.2, C62.2, C63.2, C64.2, C65.2, J97.1, J99.1, J102.1, J103.1, J104.1, R124.1, R125.1, R130.1, U13.2, U13.10, U13.25
GND13: ADR13.1, C66.2, C67.2, C68.2, C69.2, C70.2, J105.1, J107.1, J110.1, J111.1, J112.1, R134.1, R135.1, R140.1, U14.2, U14.10, U14.25
GND14: ADR14.1, C71.2, C72.2, C73.2, C74.2, C75.2, J113.1, J115.1, J118.1, J119.1, J120.1, R144.1, R145.1, R150.1, U15.2, U15.10, U15.25
GND15: ADR15.1, C76.2, C77.2, C78.2, C79.2, C80.2, J121.1, J123.1, J126.1, J127.1, J128.1, R154.1, R155.1, R160.1, U16.2, U16.10, U16.25
GND16: ADR16.1, C81.2, C82.2, C83.2, C84.2, C85.2, J129.1, J131.1, J134.1, J135.1, J136.1, R164.1, R165.1, R170.1, U17.2, U17.10, U17.25
GND17: ADR17.1, C86.2, C87.2, C88.2, C89.2, C90.2, J137.1, J139.1, J142.1, J143.1, J144.1, R174.1, R175.1, R180.1, U18.2, U18.10, U18.25
GND18: ADR18.1, C91.2, C92.2, C93.2, C94.2, C95.2, J145.1, J147.1, J150.1, J151.1, J152.1, R184.1, R185.1, R190.1, U19.2, U19.10, U19.25
GND19: ADR19.1, C96.2, C97.2, C98.2, C99.2, C100.2, J153.1, J155.1, J158.1, J159.1, J160.1, R194.1, R195.1, R200.1, U20.2, U20.10, U20.25
GND20: ADR20.1, C101.2, C102.2, C103.2, C104.2, C105.2, J161.1, J163.1, J166.1, J167.1, J168.1, R204.1, R205.1, R210.1, U21.2, U21.10, U21.25
GND21: ADR21.1, C106.2, C107.2, C108.2, C109.2, C110.2, J169.1, J171.1, J174.1, J175.1, J176.1, R214.1, R215.1, R220.1, U22.2, U22.10, U22.25
GND22: ADR22.1, C111.2, C112.2, C113.2, C114.2, C115.2, J177.1, J179.1, J182.1, J183.1, J184.1, R224.1, R225.1, R230.1, U23.2, U23.10, U23.25
GND23: ADR23.1, C116.2, C117.2, C118.2, C119.2, C120.2, J185.1, J187.1, J190.1, J191.1, J192.1, R234.1, R235.1, R240.1, U24.2, U24.10, U24.25
unnamed: C5.1, U2.27, Y1.P$2
unnamed: C3.1, U2.26, Y1.P$1
unnamed: PWR.C, R2.2
unnamed: LED.2, PWR.A
unnamed: C10.1, U1.27, Y2.P$2
unnamed: C9.1, U1.26, Y2.P$1
unnamed: PWR1.C, R20.2
unnamed: LED1.2, PWR1.A
unnamed: C15.1, U3.27, Y3.P$2
unnamed: C14.1, U3.26, Y3.P$1
unnamed: PWR2.C, R30.2
unnamed: LED2.2, PWR2.A
unnamed: C20.1, U4.27, Y4.P$2
unnamed: C19.1, U4.26, Y4.P$1
unnamed: PWR3.C, R40.2
unnamed: LED3.2, PWR3.A
unnamed: C25.1, U5.27, Y5.P$2
unnamed: C24.1, U5.26, Y5.P$1
unnamed: PWR4.C, R50.2
unnamed: LED4.2, PWR4.A
unnamed: C30.1, U6.27, Y6.P$2
unnamed: C29.1, U6.26, Y6.P$1
unnamed: PWR5.C, R60.2
unnamed: LED5.2, PWR5.A
unnamed: C35.1, U7.27, Y7.P$2
unnamed: C34.1, U7.26, Y7.P$1
unnamed: PWR6.C, R70.2
unnamed: LED6.2, PWR6.A
unnamed: C40.1, U8.27, Y8.P$2
unnamed: C39.1, U8.26, Y8.P$1
unnamed: PWR7.C, R80.2
unnamed: LED7.2, PWR7.A
unnamed: C45.1, U9.27, Y9.P$2
unnamed: C44.1, U9.26, Y9.P$1
unnamed: PWR8.C, R90.2
unnamed: LED8.2, PWR8.A
unnamed: C50.1, U10.27, Y10.P$2
unnamed: C49.1, U10.26, Y10.P$1
unnamed: PWR9.C, R100.2
unnamed: LED9.2, PWR9.A
unnamed: C55.1, U11.27, Y11.P$2
unnamed: C54.1, U11.26, Y11.P$1
unnamed: PWR10.C, R110.2
unnamed: LED10.2, PWR10.A
unnamed: C60.1, U12.27, Y12.P$2
unnamed: C59.1, U12.26, Y12.P$1
unnamed: PWR11.C, R120.2
unnamed: LED11.2, PWR11.A
unnamed: C65.1, U13.27, Y13.P$2
unnamed: C64.1, U13.26, Y13.P$1
unnamed: PWR12.C, R130.2
unnamed: LED12.2, PWR12.A
unnamed: C70.1, U14.27, Y14.P$2
unnamed: C69.1, U14.26, Y14.P$1
unnamed: PWR13.C, R140.2
unnamed: LED13.2, PWR13.A
unnamed: C75.1, U15.27, Y15.P$2
unnamed: C74.1, U15.26, Y15.P$1
unnamed: PWR14.C, R150.2
unnamed: LED14.2, PWR14.A
unnamed: C80.1, U16.27, Y16.P$2
unnamed: C79.1, U16.26, Y16.P$1
unnamed: PWR15.C, R160.2
unnamed: LED15.2, PWR15.A
unnamed: C85.1, U17.27, Y17.P$2
unnamed: C84.1, U17.26, Y17.P$1
unnamed: PWR16.C, R170.2
unnamed: LED16.2, PWR16.A
unnamed: C90.1, U18.27, Y18.P$2
unnamed: C89.1, U18.26, Y18.P$1
unnamed: PWR17.C, R180.2
unnamed: LED17.2, PWR17.A
unnamed: C95.1, U19.27, Y19.P$2
unnamed: C94.1, U19.26, Y19.P$1
unnamed: PWR18.C, R190.2
unnamed: LED18.2, PWR18.A
unnamed: C100.1, U20.27, Y20.P$2
unnamed: C99.1, U20.26, Y20.P$1
unnamed: PWR19.C, R200.2
unnamed: LED19.2, PWR19.A
unnamed: C105.1, U21.27, Y21.P$2
unnamed: C104.1, U21.26, Y21.P$1
unnamed: PWR20.C, R210.2
unnamed: LED20.2, PWR20.A
unnamed: C110.1, U22.27, Y22.P$2
unnamed: C109.1, U22.26, Y22.P$1
unnamed: PWR21.C, R220.2
unnamed: LED21.2, PWR21.A
unnamed: C115.1, U23.27, Y23.P$2
unnamed: C114.1, U23.26, Y23.P$1
unnamed: PWR22.C, R230.2
unnamed: LED22.2, PWR22.A
unnamed: C120.1, U24.27, Y24.P$2
unnamed: C119.1, U24.26, Y24.P$1
unnamed: PWR23.C, R240.2
unnamed: LED23.2, PWR23.A
PS0/WAKE: J6.7, J8.2, PS0.2, R7.2, U2.6
PS0/WAKE1: J9.7, J13.2, PS2.2, R14.2, U1.6
PS0/WAKE2: J17.7, J21.2, PS4.2, R24.2, U3.6
PS0/WAKE3: J25.7, J29.2, PS6.2, R34.2, U4.6
PS0/WAKE4: J33.7, J37.2, PS8.2, R44.2, U5.6
PS0/WAKE5: J41.7, J45.2, PS10.2, R54.2, U6.6
PS0/WAKE6: J49.7, J53.2, PS12.2, R64.2, U7.6
PS0/WAKE7: J57.7, J61.2, PS14.2, R74.2, U8.6
PS0/WAKE8: J65.7, J69.2, PS16.2, R84.2, U9.6
PS0/WAKE9: J73.7, J77.2, PS18.2, R94.2, U10.6
PS0/WAKE10: J81.7, J85.2, PS20.2, R104.2, U11.6
PS0/WAKE11: J89.7, J93.2, PS22.2, R114.2, U12.6
PS0/WAKE12: J97.7, J101.2, PS24.2, R124.2, U13.6
PS0/WAKE13: J105.7, J109.2, PS26.2, R134.2, U14.6
PS0/WAKE14: J113.7, J117.2, PS28.2, R144.2, U15.6
PS0/WAKE15: J121.7, J125.2, PS30.2, R154.2, U16.6
PS0/WAKE16: J129.7, J133.2, PS32.2, R164.2, U17.6
PS0/WAKE17: J137.7, J141.2, PS34.2, R174.2, U18.6
PS0/WAKE18: J145.7, J149.2, PS36.2, R184.2, U19.6
PS0/WAKE19: J153.7, J157.2, PS38.2, R194.2, U20.6
PS0/WAKE20: J161.7, J165.2, PS40.2, R204.2, U21.6
PS0/WAKE21: J169.7, J173.2, PS42.2, R214.2, U22.6
PS0/WAKE22: J177.7, J181.2, PS44.2, R224.2, U23.6
PS0/WAKE23: J185.7, J189.2, PS46.2, R234.2, U24.6
PS1: J8.1, PS1.2, R8.2, U2.5
PS2: J13.1, PS3.2, R15.2, U1.5
PS3: J21.1, PS5.2, R25.2, U3.5
PS4: J29.1, PS7.2, R35.2, U4.5
PS5: J37.1, PS9.2, R45.2, U5.5
PS6: J45.1, PS11.2, R55.2, U6.5
PS7: J53.1, PS13.2, R65.2, U7.5
PS8: J61.1, PS15.2, R75.2, U8.5
PS9: J69.1, PS17.2, R85.2, U9.5
PS10: J77.1, PS19.2, R95.2, U10.5
PS11: J85.1, PS21.2, R105.2, U11.5
PS12: J93.1, PS23.2, R115.2, U12.5
PS13: J101.1, PS25.2, R125.2, U13.5
PS14: J109.1, PS27.2, R135.2, U14.5
PS15: J117.1, PS29.2, R145.2, U15.5
PS16: J125.1, PS31.2, R155.2, U16.5
PS17: J133.1, PS33.2, R165.2, U17.5
PS18: J141.1, PS35.2, R175.2, U18.5
PS19: J149.1, PS37.2, R185.2, U19.5
PS20: J157.1, PS39.2, R195.2, U20.5
PS21: J165.1, PS41.2, R205.2, U21.5
PS22: J173.1, PS43.2, R215.2, U22.5
PS23: J181.1, PS45.2, R225.2, U23.5
PS24: J189.1, PS47.2, R235.2, U24.5
SCL/SCK/RX: J1.4, J2.4, J3.4, J4.4, J6.3, R12.1, U2.19
SCL/SCK/RX1: J9.3, J11.4, J14.4, J15.4, J16.4, R18.1, U1.19
SCL/SCK/RX2: J17.3, J19.4, J22.4, J23.4, J24.4, R28.1, U3.19
SCL/SCK/RX3: J25.3, J27.4, J30.4, J31.4, J32.4, R38.1, U4.19
SCL/SCK/RX4: J33.3, J35.4, J38.4, J39.4, J40.4, R48.1, U5.19
SCL/SCK/RX5: J41.3, J43.4, J46.4, J47.4, J48.4, R58.1, U6.19
SCL/SCK/RX6: J49.3, J51.4, J54.4, J55.4, J56.4, R68.1, U7.19
SCL/SCK/RX7: J57.3, J59.4, J62.4, J63.4, J64.4, R78.1, U8.19
SCL/SCK/RX8: J65.3, J67.4, J70.4, J71.4, J72.4, R88.1, U9.19
SCL/SCK/RX9: J73.3, J75.4, J78.4, J79.4, J80.4, R98.1, U10.19
SCL/SCK/RX10: J81.3, J83.4, J86.4, J87.4, J88.4, R108.1, U11.19
SCL/SCK/RX11: J89.3, J91.4, J94.4, J95.4, J96.4, R118.1, U12.19
SCL/SCK/RX12: J97.3, J99.4, J102.4, J103.4, J104.4, R128.1, U13.19
SCL/SCK/RX13: J105.3, J107.4, J110.4, J111.4, J112.4, R138.1, U14.19
SCL/SCK/RX14: J113.3, J115.4, J118.4, J119.4, J120.4, R148.1, U15.19
SCL/SCK/RX15: J121.3, J123.4, J126.4, J127.4, J128.4, R158.1, U16.19
SCL/SCK/RX16: J129.3, J131.4, J134.4, J135.4, J136.4, R168.1, U17.19
SCL/SCK/RX17: J137.3, J139.4, J142.4, J143.4, J144.4, R178.1, U18.19
SCL/SCK/RX18: J145.3, J147.4, J150.4, J151.4, J152.4, R188.1, U19.19
SCL/SCK/RX19: J153.3, J155.4, J158.4, J159.4, J160.4, R198.1, U20.19
SCL/SCK/RX20: J161.3, J163.4, J166.4, J167.4, J168.4, R208.1, U21.19
SCL/SCK/RX21: J169.3, J171.4, J174.4, J175.4, J176.4, R218.1, U22.19
SCL/SCK/RX22: J177.3, J179.4, J182.4, J183.4, J184.4, R228.1, U23.19
SCL/SCK/RX23: J185.3, J187.4, J190.4, J191.4, J192.4, R238.1, U24.19
SCL_PU: I2C.1, R12.2
SCL_PU1: I2C1.1, R18.2
SCL_PU2: I2C2.1, R28.2
SCL_PU3: I2C3.1, R38.2
SCL_PU4: I2C4.1, R48.2
SCL_PU5: I2C5.1, R58.2
SCL_PU6: I2C6.1, R68.2
SCL_PU7: I2C7.1, R78.2
SCL_PU8: I2C8.1, R88.2
SCL_PU9: I2C9.1, R98.2
SCL_PU10: I2C10.1, R108.2
SCL_PU11: I2C11.1, R118.2
SCL_PU12: I2C12.1, R128.2
SCL_PU13: I2C13.1, R138.2
SCL_PU14: I2C14.1, R148.2
SCL_PU15: I2C15.1, R158.2
SCL_PU16: I2C16.1, R168.2
SCL_PU17: I2C17.1, R178.2
SCL_PU18: I2C18.1, R188.2
SCL_PU19: I2C19.1, R198.2
SCL_PU20: I2C20.1, R208.2
SCL_PU21: I2C21.1, R218.2
SCL_PU22: I2C22.1, R228.2
SCL_PU23: I2C23.1, R238.2
SDA/MISO/TX: J1.5, J2.3, J3.3, J4.3, J6.4, R13.1, U2.20
SDA/MISO/TX1: J9.4, J11.5, J14.3, J15.3, J16.3, R19.1, U1.20
SDA/MISO/TX2: J17.4, J19.5, J22.3, J23.3, J24.3, R29.1, U3.20
SDA/MISO/TX3: J25.4, J27.5, J30.3, J31.3, J32.3, R39.1, U4.20
SDA/MISO/TX4: J33.4, J35.5, J38.3, J39.3, J40.3, R49.1, U5.20
SDA/MISO/TX5: J41.4, J43.5, J46.3, J47.3, J48.3, R59.1, U6.20
SDA/MISO/TX6: J49.4, J51.5, J54.3, J55.3, J56.3, R69.1, U7.20
SDA/MISO/TX7: J57.4, J59.5, J62.3, J63.3, J64.3, R79.1, U8.20
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
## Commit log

2023-06-28 Starting from v10 version of BNO080
2023-06-28 Silk updated to BNO086 and vectors
    -Product name silk updated to BNO086
    -all silk updated to vector buzzard style
    -Jumpers updated to newest packages
2023-06-28 datasheet and SHTP doc
2023-06-28 Ordering instructions added
2023-06-28 minor stuff - measures, library work
    -added measures and units
    -replaced some connectors, fids, standoffs, GND symbols to newer libraries.
    -renamed jumpers (in SCH) to match silk names (on board).
    -Red LED to new King Bright version, also updated resistor value to 4.7K
    -some minor schematic cleanup
2023-06-28 update file name to match product
2023-06-28 some more final changes
    -added name to revisioner on sch and brd
    -moved sch section names to symbol layer, added IMU name
    -fixed two DRC errors (angle and stub)
    -added more GND vias
    -Axis labels - break linear line to show rotation line going over
    -Larger SFE flame logo
2023-06-29 3V3 net to thicker trace and more
    -upped 3v3 trace to 20mil
    -nudges some vias/traces for better GND flow
    -added more gnd vias
    -reduced GND pour isolates from 12 to 10
    -I2C pullup jumper changes to NC trace
    -updated IC to 086, in temp library for now
2023-06-29 line in sch to dash, address options in silk
    -corrected a line in SCH to match others as dashed
    -Added bottom silk to show address options
2023-06-30 production panel and gerbers v10
2023-08-15 updated ds and add other docs
    -update datasheet to latest at this time v1.16
    -add migration guide (this is the latest even though its intended for the 080/085)
    -add tare function usage guide
2023-08-16 Update README.md
    Link tutorial
2023-08-17 Include updated Serial Cube Demo
2023-08-21 Push Initial Docs to Repo
2023-08-21 Formatting Update
    Center all images used in tables by placing them in center and middle
2023-08-25 Adjust Image Formatting
2023-10-17 Add Circuit Diagrams for UART and SPI, link Fritzing Part
2023-10-17 Minor Clean up
2023-11-14 Remove "Hide" from Style
    - Remove the "hide" from the style to ensure that the images/tutorials show up when printing
2023-11-27 Update Modified Example and Add Notes
    - Update Modified example to work with Processing
    - Include Additional Notes for SAMD51
2023-11-29 Ex11 Raw Readings Screenshot update
2023-11-30 Adding Hillscrest's Self Calibration document
    Added calibration pdf to resources
2023-12-01 Deployed dd95ac5 with MkDocs version: 1.5.3
2024-08-05 Deployed 166e19c with MkDocs version: 1.6.0
2024-10-28 Add cookies
2024-10-29 Deployed c5a5199 with MkDocs version: 1.6.1
2026-06-03 Deployed fc8ed69 with MkDocs version: 1.6.1
